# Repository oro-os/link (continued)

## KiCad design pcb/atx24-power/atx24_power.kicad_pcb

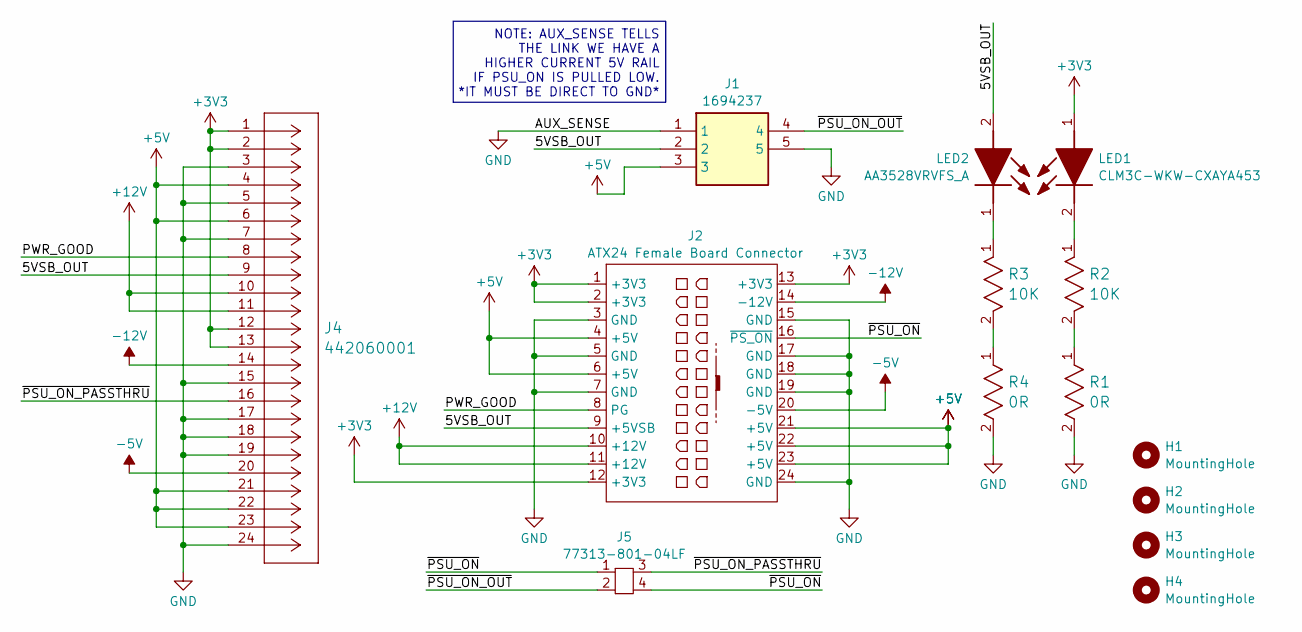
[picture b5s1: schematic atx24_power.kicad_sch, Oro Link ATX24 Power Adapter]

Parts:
H1, H2, H3, H4: MountingHole; MountingHole_3.2mm_M3
J1: 1694237; Manufacturer_Part_Number 1694237; Mouser Part Number 651-1694237
J2: ATX24 Female Board Connector; ATX24_Female_Board_Connector
J4: 442060001; CONN_SDA-44206-001_24_BP_MOL; Mouser ID 538-44206-0001
J5: 77313-801-04LF; 2x2 4p 2.54 pitch straight; Mouser ID Number 649-77313-801-04LF
LED1: CLM3C-WKW-CXAYA453; CLM3CWKWCXAYA453; Manufacturer_Part_Number CLM3C-WKW-CXAYA453; Mouser Part Number 941-CLM3CWKWCXAYA453
LED2: AA3528VRVFS_A; AA3528VRVFSA; Manufacturer_Part_Number AA3528VRVFS/A; Mouser Part Number 604-AA3528VRVFS/A
R1, R4: 0R; RES_RK73Z1E_KOA; DigiKey ID 2019-RK73Z1ETTPCT-ND
R2, R3: 10K; STA_RMCF0402_STP; DigiKey ID RMCF0402FT10K0CT-ND

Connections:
+3V3: J2.1 (+3V3), J2.2 (+3V3), J2.12 (+3V3), J2.13 (+3V3), J4.1, J4.2, J4.12, J4.13, LED1.1 (A)
+5V: J1.3, J2.4 (+5V), J2.6 (+5V), J2.21 (+5V), J2.22 (+5V), J2.23 (+5V), J4.4, J4.6, J4.21, J4.22, J4.23
+12V: J2.10 (+12V), J2.11 (+12V), J4.10, J4.11
-5V: J2.20 (-5V), J4.20
-12V: J2.14 (-12V), J4.14
/5VSB_OUT: J1.2, J2.9 (+5VSB), J4.9, LED2.2 (A)
/PWR_GOOD: J2.8 (PG), J4.8
/~PSU_ON_OUT: J1.4, J5.2
/~PSU_ON_PASSTHRU: J4.16, J5.3
/~PSU_ON: J2.16 (~PS_ON), J5.1, J5.4
GND: J1.1, J1.5, J2.3 (GND), J2.5 (GND), J2.7 (GND), J2.15 (GND), J2.17 (GND), J2.18 (GND), J2.19 (GND), J2.24 (GND), J4.3, J4.5, J4.7, J4.15, J4.17, J4.18, J4.19, J4.24, R1.2, R4.2
unnamed: LED1.2 (K), R2.1
unnamed: LED2.1 (K), R3.1
unnamed: R1.1, R2.2
unnamed: R3.2, R4.1

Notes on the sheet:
NOTE: AUX_SENSE TELLS THE LINK WE HAVE A HIGHER CURRENT 5V RAIL IF PSU_ON IS PULLED LOW. *IT MUST BE DIRECT TO GND*

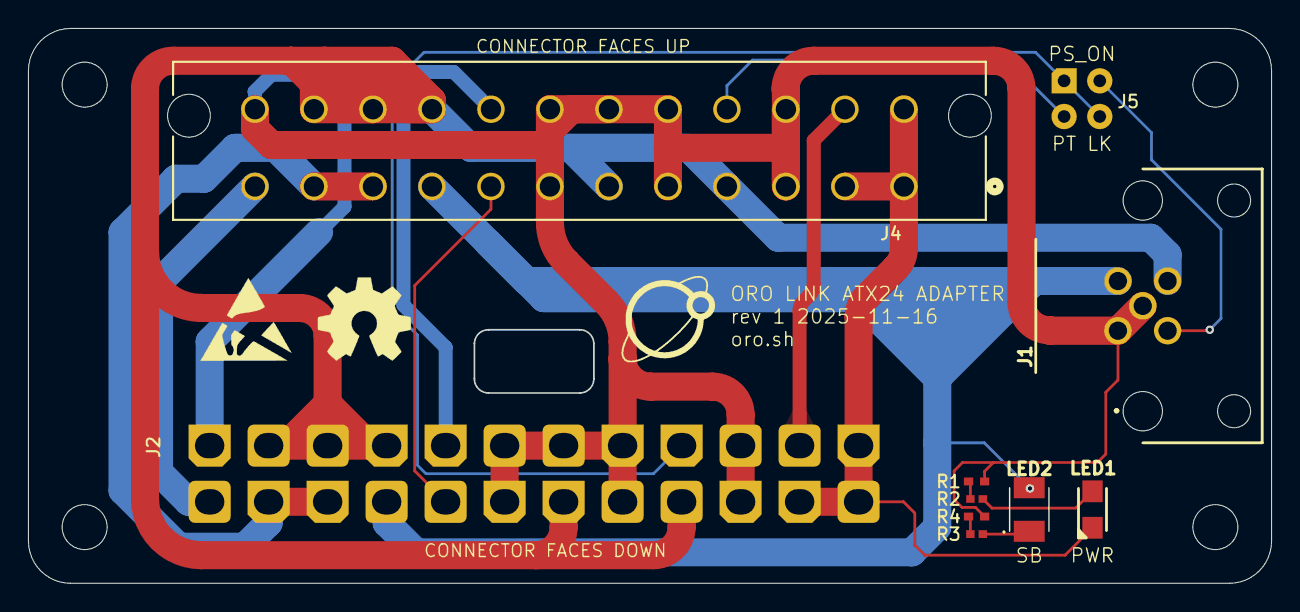
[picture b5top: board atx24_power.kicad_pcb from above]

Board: 2 copper layers, 88.5 x 39.5 mm, 14 parts (1 on the bottom side), 15 nets.

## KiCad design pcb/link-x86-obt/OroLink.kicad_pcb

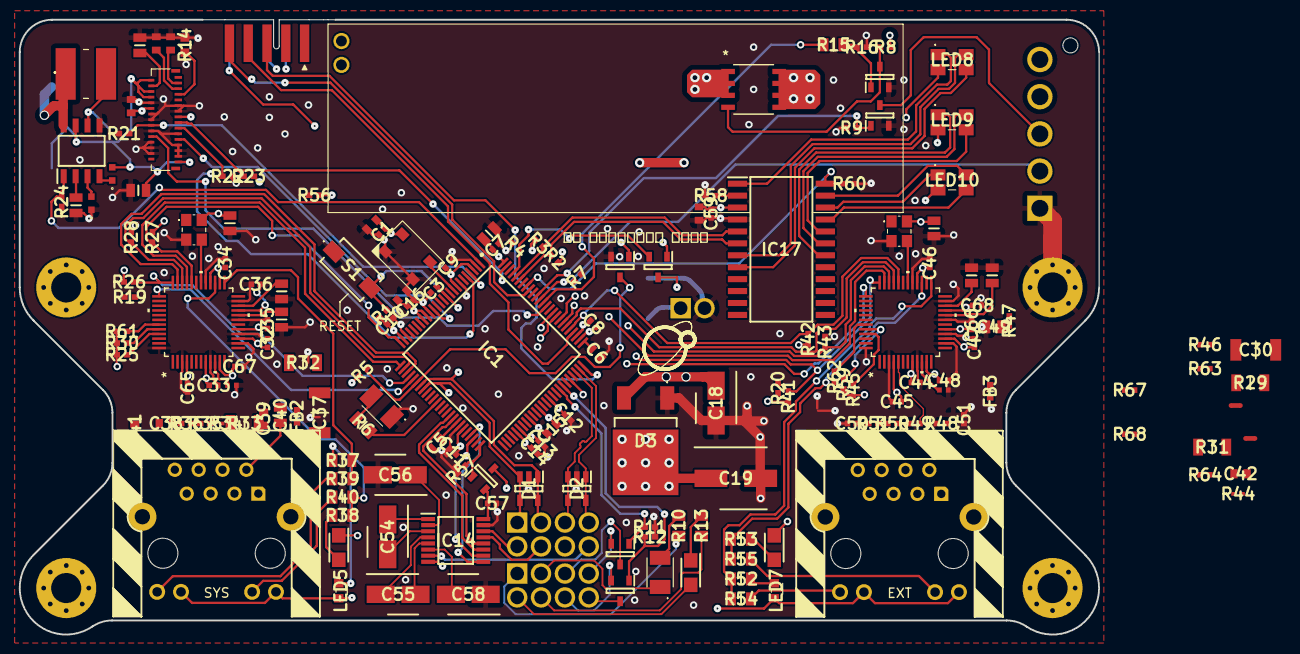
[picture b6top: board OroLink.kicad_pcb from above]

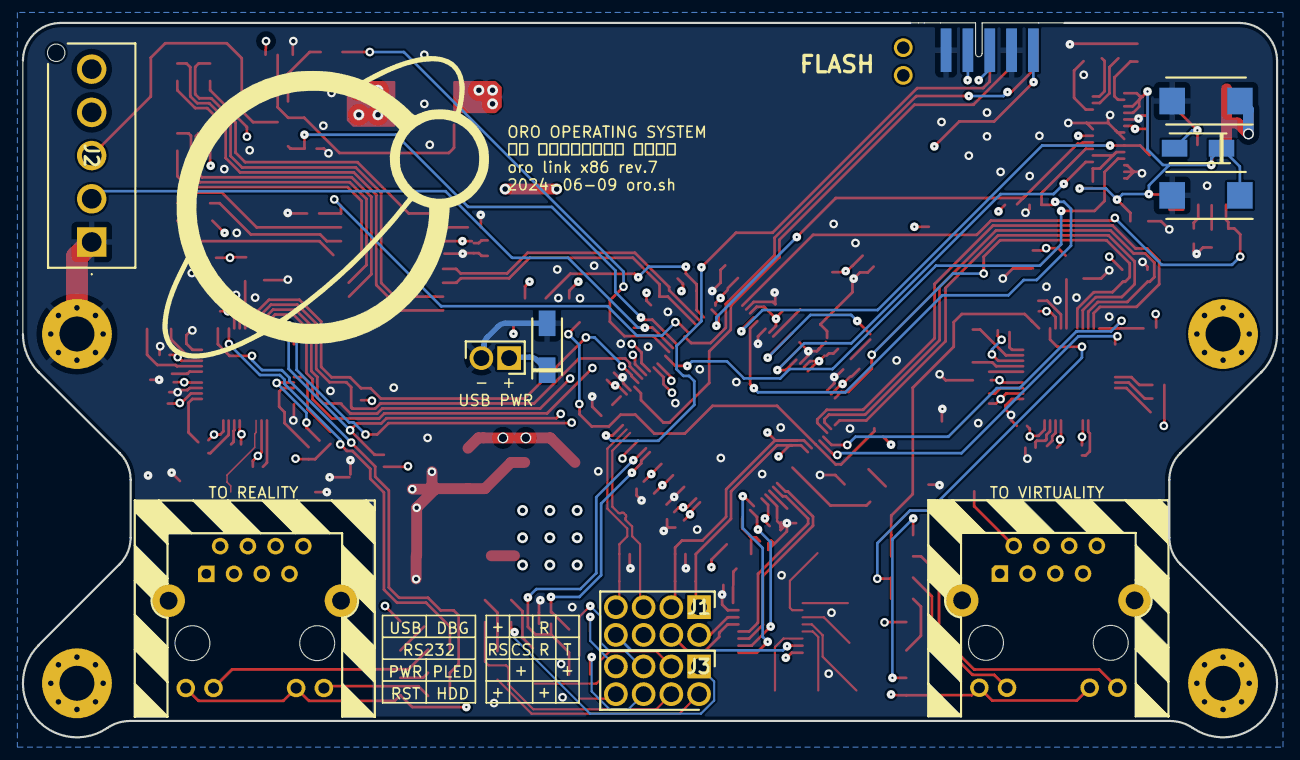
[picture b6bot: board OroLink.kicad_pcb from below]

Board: 4 copper layers, 114.9 x 65.4 mm, 183 parts (10 on the bottom side), 151 nets.

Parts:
C1, C3, C7, C8, C9, C10, C11, C12, C13, C14, C16, C32, C33, C34, C35, C36, C44, C45, C46, C47, C48, C57, C59, C65, C66, C67, C68: 0.1u; CAPC1005X33N
C2, C17, C20, C21, C23, C60: 1u; CAPC1608X90N
C4, C22, C24, C61, C62: 4.7u; CAPC2012X135N
C5, C6, C15: 2.2u; CAPC1608X90N
C18: 10u; CAPAE430X610N
C19: 22u; CAPAE660X800N
C25, C31, C40, C43, C49, C63, C64: 0.01u; CAPC2012X75N
C26: 0.047u; C1608_Commercial_Tight
C27: 0.001u; C1608_Commercial_Tight
C28, C29: 33u; CAPPM7343X310N
C30, C37: 1nF 3kV; CAPC4620X220N
C38, C39, C41, C42: 6.8nF; CAPC1608X87N
C50, C51: 22nF; CAPC1005X55N
C54, C55, C56, C58: 0.1u; CAPAE430X610N
D1, D2: ESDS302DBVR; SOT95P280X145-5N
D3: AZ1084CD-3.3TRG1; AZ1084CD33TRG1
D4, D5: SS12; DIOM5227X250N
FB1: CD54NP-180MC; CD54NP180MC
FB2, FB3: BLM18BB600SZ1D; BLM18EG121SH1D
H1, H2, H3, H4: MountingHole_Pad; MountingHole_3.2mm_M3_Pad_Via
IC1: STM32F479VGT6; QFP50P1600X1600X160-100N
IC2, IC12, IC13, IC15: PMV20ENR; SOT95P230X110-3N
IC4: TPS6734ID; SOIC127P600X175-8N
IC14: SN75C3232EPWR; SOP65P640X120-16N
IC17: IS31FL3218-GRLS2; SOIC127P1036X265-24N
J1, J3: 67996-408HLF; HDRV8W89P254_2X4_1016X483X858P
J2: DF63-5P-3.96DSA; DF635P396DSA
J4: 3-2328724-1; 323287241_flipped
J5, J6: 74990101241
J7: 2P SHORT; 2P_SHORT
J8: STLINK-V3MINIE; 009159010061911
J9: 67996-408HLF (2P CUT); HDRV8W89P254_2X4_1016X483X858P_2P
LED1, LED2: AA3528VRVFS/A; AA3528VRVFSA
LED3, LED4, LED6: CLM3C-WKW-CXAYA453; CLM3CWKWCXAYA453
LED5, LED7: APT1608VRCXF_A-5MAV; APT1608VRCXFA5MAV
LED8, LED9, LED10: 150120M173000
NT1, NT2: NetTie_2; NetTie-2_SMD_Pad0.5mm
Q1, Q2, Q3: PMV20ENR; SOT95P230X110-3N
Q4: SI4403DDY-T1-GE3; SO-8_MS-012_VIS
R1, R4, R5, R7, R8, R9, R11, R12, R16, R19, R20, R21, R22, R23, R24, R25, R26, R27, R28, R30, R41, R42, R43, R45, R56, R57, R58, R59, R60, R61, R62: 10k; RESC1005X40N
R2, R3: 4.7k; RESC1005X40N
R6, R10, R13, R15, R37, R38, R52, R53: 1k; RESC2012X60N
R14: 510K; RESC1608X55N
R17, R18: 12.4K 1%; RES_CRCW_0402
R29, R31, R32, R33: 82R <=1%; RESC3216X60N
R34, R44: 10R <=1%; RESC0603X26N
R35, R36, R50, R51: 49.9R <=1%; RESC1005X35N
R39, R40, R54, R55: 470R; RESC2012X60N
R46, R47, R48, R49, R63, R64, R67, R68: 33R <=1%; RCS0402_E3
S1: TL6400AF160QJ
U1, U2: W5500; 48LQFP_W5500_WIZ
X1: 7P-26.000MBP-T
Y1, Y2: 25MHz; ASE24576MHZLCT

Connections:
+3V3: C1.2, C2.2, C4.1, C7.2, C8.2, C9.2, C10.2, C11.2, C12.2, C13.2, C14.2, C15.1, C16.2, C17.2, C19.1, C23.2, C31.1, C32.1, C33.1, C34.1, C35.1, C36.1, C43.1, C44.1, C45.1, C46.1, C47.1, C48.1, C59.1, C60.2, C65.1, C66.1, C67.1, C68.1, D3.2 (OUTPUT), FB2.1, FB3.1, IC1.3 (VBAT), IC1.8 (VDD_1), IC1.17 (VREF+), IC1.18 (VDDA), IC1.24 (VDD_2), IC1.45 (VDD_3), IC1.55 (VDDDSI), IC1.56 (VCAPDSI), IC1.62 (VDD12DSI), IC1.65 (VDDUSB), IC1.77 (VDD_4), IC1.100 (VDD_5), IC12.3, IC15.3, IC17.3 (VCC), J4.12, J4.15, J5.9 (YLED_A), J5.11 (GLED_A), J6.9 (YLED_A), J6.11 (GLED_A), J7.1, J8.10 (VCC), LED4.1, LED5.2, LED6.1, LED7.2, LED8.2 (A_G), LED9.2 (A_G), LED10.2 (A_G), R1.1, R2.1, R3.1, R5.1, R19.2, R20.2, R23.1, R25.2, R26.2, R27.2, R30.2, R41.2, R42.2, R45.2, R59.2, R61.2, R62.2, U1.4 (AVDD), U1.8 (AVDD), U1.11 (AVDD), U1.15 (AVDD), U1.17 (AVDD), U1.21 (AVDD), U1.28 (VDD), U2.4 (AVDD), U2.8 (AVDD), U2.11 (AVDD), U2.15 (AVDD), U2.17 (AVDD), U2.21 (AVDD), U2.28 (VDD), X1.6 (VCC), Y1.4 (VDD), Y2.4 (VDD)
+5V: C18.1, C28.1, D3.3 (INPUT), FB1.1, IC4.8 (VCC), J2.5, Q4.1, Q4.2, Q4.3, R8.1
/COM Bus Header/C1+: C54.1, IC14.1 (C1+)
/COM Bus Header/C1-: C54.2, IC14.3 (C1-)
/COM Bus Header/C2+: C55.1, IC14.4 (C2+)
/COM Bus Header/C2-: C55.2, IC14.5 (C2-)
/COM Bus Header/CTS: IC1.47 (PB13), IC14.9 (ROUT2)
/COM Bus Header/EN: IC1.50 (PD8), IC15.1, R57.1
/COM Bus Header/EN_3V3: C57.1, IC14.16 (VCC), IC15.2
/COM Bus Header/RS232_CTS: IC14.8 (RIN2), J1.6
/COM Bus Header/RS232_RTS: IC14.7 (DOUT2), J1.8
/COM Bus Header/RS232_RX: IC14.13 (RIN1), J1.4
/COM Bus Header/RS232_TX: IC14.14 (DOUT1), J1.2
/COM Bus Header/RTS: IC1.48 (PB14), IC14.10 (DIN2)
/COM Bus Header/RX: IC1.42 (PB11), IC14.12 (ROUT1)
/COM Bus Header/TX: IC1.41 (PB10), IC14.11 (DIN1)
/COM Bus Header/V+: C56.1, IC14.2 (V+)
/COM Bus Header/V-: C58.2, IC14.6 (V-)
/External Ethernet/CS: IC1.80 (PA15), R42.1, U2.32 (SCSN)
/External Ethernet/ETH_RX_R+: C39.1, R31.1, R64.2
/External Ethernet/ETH_RX_R-: C42.1, R33.1, R49.2
/External Ethernet/ETH_RX_X+: C39.2, J6.1 (TD+)
/External Ethernet/ETH_RX_X-: C42.2, J6.3 (TD-)
/External Ethernet/ETH_TPIN+: R64.1, U2.6 (RXP)
/External Ethernet/ETH_TPIN-: R49.1, U2.5 (RXN)
/External Ethernet/ETH_TPOUT+: R47.1, U2.2 (TXP)
/External Ethernet/ETH_TPOUT-: R68.1, U2.1 (TXN)
/External Ethernet/ETH_TX_R+: J6.4 (RD+), R47.2, R50.1
/External Ethernet/ETH_TX_R-: J6.6 (RD-), R51.1, R68.2
/External Ethernet/GLED+: R52.2, R54.2, U2.25 (LINKLED)
/External Ethernet/RJ_EARTH: C37.1, J6.14 (MNT)
/External Ethernet/RJ_EARTH_GND: J6.8 (GNDPWR), NT2.1
/External Ethernet/SCK: IC1.81 (PC10), U2.33 (SCLK)
/External Ethernet/SDI: IC1.83 (PC12), U2.35 (MOSI)
/External Ethernet/SDO: IC1.82 (PC11), R43.2, U2.34 (MISO)
/External Ethernet/YLED+: R53.2, R55.2, U2.27 (ACTLED)
/External Ethernet/~INT: IC1.85 (PD1), R41.1, U2.36 (INTN)
/External Ethernet/~RST: IC1.84 (PD0), R20.1, U2.37 (RSTN)
/Front Panel Client/HDD+: J3.4, R13.1
/Front Panel Client/HDD-: J3.2, LED3.2
/Front Panel Client/PLED+: J3.1, R10.2
/Front Panel Client/PLED-: J3.3, LED2.1
/Front Panel Client/PWR+: J3.5, Q2.3
/Front Panel Client/PWR-: J3.7, Q2.2
/Front Panel Client/PWR_ON: IC1.68 (PC8), Q2.1, R11.1
/Front Panel Client/RESET: IC1.69 (PC9), Q3.1, R12.1
/Front Panel Client/RST+: J3.8, Q3.3
/Front Panel Client/RST-: J3.6, Q3.2
/Indicator Lights/EN: IC1.93 (PB4), IC17.24 (~SDB), R60.1
/Indicator Lights/O1: IC17.7 (O1), LED8.4 (K_R)
/Indicator Lights/O2: IC17.8 (O2), LED8.3 (K_G)
/Indicator Lights/O12: IC17.18 (O12), LED9.1 (K_B)
/Indicator Lights/O13: IC17.19 (O13), LED9.4 (K_R)
/Indicator Lights/O14: IC17.20 (O14), LED9.3 (K_G)
/Indicator Lights/O15: IC17.21 (O15), LED10.3 (K_G)
/Indicator Lights/O16: IC17.22 (O16), LED10.1 (K_B)
/Indicator Lights/O17: IC17.23 (O17), LED10.4 (K_R)
/Indicator Lights/O18: IC17.1 (O18), LED8.1 (K_B)
/Indicator Lights/SCL: IC1.95 (PB6), IC17.6 (SCL), R2.2
/Indicator Lights/SDA: IC1.96 (PB7), IC17.5 (SDA), R3.2
/Microcontroller/BOOT0: IC1.97 (BOOT0), IC12.2, R4.2
/Microcontroller/BOOT1: IC1.31 (PB2), IC13.3, R5.2
/Microcontroller/DBGUART_RX: D1.1 (NC_1), D1.5 (I/O2), IC1.32 (PE7), J1.3, J8.7 (VCP_RX)
/Microcontroller/DBGUART_TX: D1.3 (NC_2), D1.4 (I/O1), IC1.33 (PE8), J1.1, J8.8 (VCP_TX)
/Microcontroller/SWCLK: IC1.79 (PA14), J8.4 (JCLK/SWCLK)
/Microcontroller/SWDIO: IC1.75 (PA13), J8.3 (JTMS/SWDIO)
/Microcontroller/SWO: IC1.92 (PB3), J8.5 (JTDO/SWO)
/Microcontroller/SYSETH_CS: IC1.25 (PA4), R27.1, U1.32 (SCSN)
/Microcontroller/SYSETH_MISO: IC1.27 (PA6), R28.2, U1.34 (MISO)
/Microcontroller/SYSETH_SCK: IC1.26 (PA5), U1.33 (SCLK)
/Microcontroller/SYSTEH_MOSI: IC1.28 (PA7), U1.35 (MOSI)
/Microcontroller/SYSTEH_~INT: IC1.29 (PB0), R26.1, U1.36 (INTN)
/Microcontroller/SYSTEH_~RST: IC1.30 (PB1), R19.1, U1.37 (RSTN)
/Microcontroller/USB_D+: D2.1 (NC_1), D2.5 (I/O2), IC1.74 (PA12), J1.7
/Microcontroller/USB_D-: D2.3 (NC_2), D2.4 (I/O1), IC1.73 (PA11), J1.5
/Microcontroller/USB_VBUS: D5.1, IC1.71 (PA9), J9.1
/Microcontroller/VCAP1: C5.1, IC1.43 (VCAP1)
/Microcontroller/VCAP2: C6.1, IC1.76 (VCAP2)
/OLED Socket/+12V: C22.1, C27.2, C29.1, D4.1, IC4.7 (FB), J4.2, J4.6, J4.8, J4.31
/OLED Socket/CS: IC1.99 (PB9), J4.17, R23.2
/OLED Socket/DC: IC1.5 (PC14), J4.19, R22.1
/OLED Socket/ENABLE: IC1.1 (PE2), IC4.1 (EN), R24.1
/OLED Socket/SCK: IC1.87 (PD3), J4.22
/OLED Socket/SDI: IC1.15 (PC3), J4.23
/OLED Socket/~RST: IC1.4 (PC13), J4.18, R21.1
/Power Supply/5VSB_ON: J2.4, Q4.5, Q4.6, Q4.7, Q4.8
/Power Supply/PSU_ON: J2.3, Q1.3
/Power Supply/PW_OK: IC1.89 (PD5), J2.2, R7.1
/Power Supply/PW_ON: IC1.90 (PD6), Q1.1, R9.1
/Power Supply/PW_SB: IC1.88 (PD4), R15.2
/System Ethernet/ETH_RX_R+: C38.1, R29.1, R63.2
/System Ethernet/ETH_RX_R-: C41.1, R32.1, R48.2
/System Ethernet/ETH_RX_X+: C38.2, J5.1 (TD+)
/System Ethernet/ETH_RX_X-: C41.2, J5.3 (TD-)
/System Ethernet/ETH_TPIN+: R63.1, U1.6 (RXP)
/System Ethernet/ETH_TPIN-: R48.1, U1.5 (RXN)
/System Ethernet/ETH_TPOUT+: R46.1, U1.2 (TXP)
/System Ethernet/ETH_TPOUT-: R67.1, U1.1 (TXN)
/System Ethernet/ETH_TX_R+: J5.4 (RD+), R35.1, R46.2
/System Ethernet/ETH_TX_R-: J5.6 (RD-), R36.1, R67.2
/System Ethernet/GLED+: R37.2, R39.2, U1.25 (LINKLED)
/System Ethernet/RJ_EARTH: C30.1, J5.14 (MNT)
/System Ethernet/RJ_EARTH_GND: J5.8 (GNDPWR), NT1.1
/System Ethernet/YLED+: R38.2, R40.2, U1.27 (ACTLED)
GND: C1.1, C2.1, C3.2, C4.2, C5.2, C6.2, C7.1, C8.1, C9.1, C10.1, C11.1, C12.1, C13.1, C14.1, C15.2, C16.1, C17.1, C18.2, C19.2, C20.1, C21.1, C22.2, C23.1, C24.1, C25.1, C26.1, C28.2, C29.2, C30.2, C31.2, C32.2, C33.2, C34.2, C35.2, C36.2, C37.2, C40.2, C43.2, C44.2, C45.2, C46.2, C47.2, C48.2, C49.2, C50.2, C51.2, C56.2, C57.2, C58.1, C59.2, C60.1, C61.1, C62.1, C63.2, C64.2, C65.2, C66.2, C67.2, C68.2, D1.2 (GND), D2.2 (GND), D3.1 (GND), D5.2, H4.1, IC1.2 (VSS_1), IC1.7 (VSS_2), IC1.16 (VSSA), IC1.23 (VSS_3), IC1.44 (VSS_4), IC1.59 (VSSDSI), IC1.78 (VSS_5), IC2.2, IC4.5 (GND), IC13.2, IC14.15 (GND), IC17.4 (GND), J2.1, J4.10, J4.11, J4.13, J4.14, J4.16, J4.20, J4.21, J4.24, J4.25, J4.26, J4.27, J4.28, J4.29, J8.6 (GND), J8.9 (NRST), J9.2, LED1.1, NT1.2, NT2.2, Q1.2, R4.1, R7.2, R9.2, R11.2, R12.2, R14.2, R16.2, R17.2, R18.2, R21.2, R22.2, R24.2, R28.1, R43.1, R56.2, R57.2, R58.1, R60.2, S1.1 (COM), U1.3 (AGND), U1.9 (AGND), U1.14 (AGND), U1.16 (AGND), U1.19 (AGND), U1.23 (RSVD), U1.29 (GND), U1.48 (AGND), U2.3 (AGND), U2.9 (AGND), U2.14 (AGND), U2.16 (AGND), U2.19 (AGND), U2.23 (RSVD), U2.29 (GND), U2.48 (AGND), X1.1 (GND/AFC), X1.3 (GND), Y1.2 (GND/CASE), Y2.2 (GND/CASE)
unnamed: C20.2, J4.3
unnamed: C21.2, J4.5
unnamed: C24.2, J4.4
unnamed: FB2.2, R34.2, R35.2, R36.2
unnamed: FB3.2, R44.2, R50.2, R51.2
unnamed: C3.1, IC1.11 (NRST), R1.2, S1.2 (NO)
unnamed: IC1.37 (PE12), R6.1
unnamed: IC1.9 (PH0), X1.4 (CLK)
unnamed: IC2.1, R15.1, R16.1
unnamed: IC2.3, Q4.4, R8.2
unnamed: C27.1, IC4.4 (COMP)
unnamed: D4.2, FB1.2, IC4.6 (OUT)
unnamed: C25.2, IC4.2 (REF)
unnamed: C26.2, IC4.3 (SS)
unnamed: IC12.1, IC13.1, J7.2, R56.1
unnamed: IC17.2 (R_EXT), R58.2
unnamed: J4.7, R14.1
unnamed: C50.1, J5.5 (CRD), R34.1
unnamed: C40.1, J5.2 (CTD), R29.2, R32.2
unnamed: J5.12 (GLED_C), R39.1
unnamed: J5.10 (YLED_C), R40.1
unnamed: C51.1, J6.5 (CRD), R44.1
unnamed: C49.1, J6.2 (CTD), R31.2, R33.2
unnamed: J6.12 (GLED_C), R54.1
unnamed: J6.10 (YLED_C), R55.1
unnamed: LED1.2, R6.2
unnamed: LED2.2, R10.1
unnamed: LED3.1, R13.2
unnamed: LED4.2, R38.1
unnamed: LED5.1, R37.1
unnamed: LED6.2, R53.1
unnamed: LED7.1, R52.1
unnamed: C63.1, U1.22 (1V20)
unnamed: R17.1, U1.10 (EXRES1)
unnamed: R25.1, U1.45 (PMODE0)
unnamed: R30.1, U1.44 (PMODE1)
unnamed: R61.1, U1.43 (PMODE2)
unnamed: C61.2, U1.20 (TOCAP)
unnamed: U1.30 (XI/CLKIN), Y1.3 (OUTPUT)
unnamed: C64.1, U2.22 (1V20)
unnamed: R18.1, U2.10 (EXRES1)
unnamed: R45.1, U2.45 (PMODE0)
unnamed: R59.1, U2.44 (PMODE1)
unnamed: R62.1, U2.43 (PMODE2)
unnamed: C62.2, U2.20 (TOCAP)
unnamed: U2.30 (XI/CLKIN), Y2.3 (OUTPUT)

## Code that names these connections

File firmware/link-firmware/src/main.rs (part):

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	nv_ram.reboot.in_progress.write(true);

	// Begin initialization
	let debug_led1 = OutputOpenDrain::new(p.PD2, Level::High, Speed::Low);
	let debug_led2 = OutputOpenDrain::new(p.PB7, Level::High, Speed::Low);
	let debug_led3 = OutputOpenDrain::new(p.PC8, Level::High, Speed::Low);

	let ind_en = Output::new(p.PB8, Level::Low, Speed::Low);

	static I2C: StaticCell<Mutex<NoopRawMutex, i2c::I2c<'static, Blocking, i2c::mode::Master>>> =
		StaticCell::new();
	let i2c = I2C.init(Mutex::<NoopRawMutex, _>::new(i2c::I2c::new_blocking(
		p.I2C3,
		p.PA8,
		p.PC9,
		{
			let mut config = i2c::Config::default();
			config.scl_pullup = false;
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
	let _usart = usart::Uart::new_with_rtscts(
		p.USART2,
		p.PD6,
		p.PA2,
		p.PA1,
		p.PD3,
		p.DMA1_CH6,
		p.DMA1_CH5,
		Irqs,
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	)
	.unwrap();

	let usb_output_selector = Output::new(p.PA7, Level::High, Speed::Low);
	let ulpi_oc = ExtiInput::new(p.PB14, p.EXTI14, Pull::None, Irqs);
	let ulpi_rst = Output::new(p.PB15, Level::Low, Speed::Low);
	static EP_OUT_BUFFER: StaticCell<[u8; 256]> = StaticCell::new();
	let ep_out_buffer = EP_OUT_BUFFER.init([0; 256]);
	let ulpi = usb::Driver::new_hs_ulpi(
		p.USB_OTG_HS,
		Irqs,
		p.PA5,
		p.PC2,
		p.PC3,
		p.PC0,
		p.PA3,
		p.PB0,
		p.PB1,
		p.PB10,
		p.PB11,
		p.PB12,
		p.PB13,
		p.PB5,
		ep_out_buffer,
		{
			let mut config = usb::Config::default();
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		StaticCell::new();
	let spi3 = SPI3.init(Mutex::new(spi::Spi::new(
		p.SPI3,
		p.PC10,
		p.PC12,
		p.PC11,
		p.DMA1_CH7,
		p.DMA1_CH0,
		Irqs,
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		},
	)));

	let sd_oc = ExtiInput::new(p.PA6, p.EXTI6, Pull::None, Irqs);
	let sd_sense = ExtiInput::new(p.PC13, p.EXTI13, Pull::None, Irqs);
	let _sd_sense_cable = ExtiInput::new(p.PD8, p.EXTI8, Pull::None, Irqs);
	// TODO(qix-): Switch back to open drain after pullup is added
	// let sd_en = OutputOpenDrain::new(p.PC14, Level::High, Speed::Low);
	let sd_en = OutputOpenDrain::new_pull(p.PC14, Level::High, Speed::Low, Pull::Up);
	let sd_cs = OutputOpenDrain::new_pull(p.PD5, Level::High, Speed::VeryHigh, Pull::Up);
	let sd_host_sut_sel = Output::new(p.PD14, Level::Low, Speed::Low);
	let sd_spi: &'static _ = spi3;

	let syseth_int = ExtiInput::new(p.PA4, p.EXTI4, Pull::None, Irqs);
	let mut syseth_rst = Output::new(p.PC15, Level::Low, Speed::VeryHigh);
	let syseth_cs = OutputOpenDrain::new(p.PD7, Level::High, Speed::VeryHigh);
	let syseth = SpiDevice::new(spi3, syseth_cs);
	let syseth_seed = self::rand::next_u64();
	reset_wiznet_chip(&mut syseth_rst).await;
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	);

	let (_uart_tx, uart_rx) =
		usart::Uart::new(p.UART7, p.PE7, p.PE8, p.DMA1_CH1, p.DMA1_CH3, Irqs, {
			let mut config = usart::Config::default();
			config.baudrate = 3_000_000;
			config.stop_bits = usart::StopBits::STOP1;
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	let uart_rx_buffer = UART_RX_BUFFER.init([0u8; 4096]);
	let _uart_rx = uart_rx.into_ring_buffered(uart_rx_buffer);

	let exteth_int = ExtiInput::new(p.PA0, p.EXTI0, Pull::None, Irqs);
	let mut exteth_int_polarity = OutputOpenDrain::new(p.PB6, Level::Low, Speed::Low);
	exteth_int_polarity.set_low(); // Enable ethernet interrupt polarity (active low)
	let mut exteth_rst = OutputOpenDrain::new(p.PD0, Level::High, Speed::VeryHigh);
	let exteth_cs = OutputOpenDrain::new(p.PE11, Level::High, Speed::VeryHigh);
	let exteth = spi::Spi::new(
		p.SPI4,
		p.PE2,
		p.PE14,
		p.PE13,
		p.DMA2_CH1,
		p.DMA2_CH0,
		Irqs,
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		exteth_seed,
	);

	let oled_rst = Output::new(p.PD1, Level::High, Speed::Low);
	let oled_cs = OutputOpenDrain::new(p.PB9, Level::High, Speed::VeryHigh);
	let oled_dc = Output::new(p.PD4, Level::Low, Speed::VeryHigh);
	let oled_en = Output::new(p.PD9, Level::Low, Speed::Low);
	let oled = spi::Spi::new_txonly(p.SPI2, p.PA9, p.PC1, p.DMA1_CH4, Irqs, {
		let mut oledconf = spi::Config::default();
		oledconf.mode = spi::MODE_0;
		oledconf.bit_order = spi::BitOrder::MsbFirst;
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		oledconf
	});

	let _gpio2 = Output::new(p.PC7, Level::Low, Speed::Low);
	let _gpio3 = Output::new(p.PA10, Level::Low, Speed::Low);
	let _gpio4 = Output::new(p.PC6, Level::Low, Speed::Low);
	let _gpio5 = Output::new(p.PB4, Level::Low, Speed::Low);

	let vbus_oc = ExtiInput::new(p.PD15, p.EXTI15, Pull::None, Irqs);
	let vbus_en = Output::new(p.PE15, Level::Low, Speed::Low);
	let aux_vbus_sense_pin = Input::new(p.PA11, Pull::None);
	// Have we sensed the aux vbus line?
	let aux_vbus_sense = aux_vbus_sense_pin.is_low();
	crate::vars::STAT_AUX_VBUS_SENSE.set(aux_vbus_sense).await;
	let aux_vbus_oc = ExtiInput::new(p.PA12, p.EXTI12, Pull::None, Irqs);
	let aux_vbus_en = OutputOpenDrain::new(p.PA15, Level::High, Speed::Low);
	// TODO: Set `Pull::None` once external pull-up has been added
	// TODO: https://github.com/oro-os/link/issues/112
	let board_power_alert = ExtiInput::new(p.PE9, p.EXTI9, Pull::Up, Irqs);
	let psu_on = Output::new(p.PD10, Level::Low, Speed::Low);
	let _sut_pwr_switch = Output::new(p.PE12, Level::Low, Speed::Low);
	let _sut_rst_switch = Output::new(p.PE10, Level::Low, Speed::Low);

	defmt::info!("initialization complete; starting services...");
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
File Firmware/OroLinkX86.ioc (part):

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Mcu.Name=STM32F479V(G-I)Tx
Mcu.Package=LQFP100
Mcu.UserName=STM32F479VGTx
PA11.GPIOParameters=GPIO_Label
PA11.GPIO_Label=USB_D-
PA11.Mode=Device_Only
PA11.Signal=USB_OTG_FS_DM
PA12.GPIOParameters=GPIO_Label
PA12.GPIO_Label=USB_D+
PA12.Mode=Device_Only
PA12.Signal=USB_OTG_FS_DP
PA13.GPIOParameters=GPIO_Label
PA13.GPIO_Label=SWDIO
PA13.Mode=Trace_Asynchronous_SW
PA13.Signal=SYS_JTMS-SWDIO
PA14.GPIOParameters=GPIO_Label
PA14.GPIO_Label=SWCLK
PA14.Mode=Trace_Asynchronous_SW
PA14.Signal=SYS_JTCK-SWCLK
PA15.GPIOParameters=GPIO_Label
PA15.GPIO_Label=EXTETH_SS
PA15.Mode=NSS_Signal_Hard_Output
PA15.Signal=SPI3_NSS
PA2.GPIOParameters=GPIO_Label
PA2.GPIO_Label=SYSETH_EN
PA2.Signal=GPIO_Output
PA3.GPIOParameters=GPIO_Label
PA3.GPIO_Label=SYSETH_XFRM_EN
PA3.Signal=GPIO_Output
PA4.GPIOParameters=GPIO_Label
PA4.GPIO_Label=SYSETH_SS
PA4.Mode=NSS_Signal_Hard_Output
PA4.Signal=SPI1_NSS
PA5.GPIOParameters=GPIO_Label
PA5.GPIO_Label=SYSETH_SCK
PA5.Mode=Full_Duplex_Master
PA5.Signal=SPI1_SCK
PA6.GPIOParameters=GPIO_Label
PA6.GPIO_Label=SYSETH_MISO
PA6.Mode=Full_Duplex_Master
PA6.Signal=SPI1_MISO
PA7.GPIOParameters=GPIO_Label
PA7.GPIO_Label=SYSETH_MOSI
PA7.Mode=Full_Duplex_Master
PA7.Signal=SPI1_MOSI
PB0.GPIOParameters=GPIO_Label
PB0.GPIO_Label=SYSETH_INT
PB0.Signal=GPXTI0
PB1.GPIOParameters=PinState,GPIO_PuPd,GPIO_Label
PB1.GPIO_Label=SYSETH_RST
PB1.GPIO_PuPd=GPIO_NOPULL
PB1.PinState=GPIO_PIN_RESET
PB1.Signal=GPIO_Output
PB10.GPIOParameters=GPIO_Label
PB10.GPIO_Label=RS232_TX
PB10.Mode=Asynchronous
PB10.Signal=USART3_TX
PB11.GPIOParameters=GPIO_Label
PB11.GPIO_Label=RS232_RX
PB11.Mode=Asynchronous
PB11.Signal=USART3_RX
PB13.GPIOParameters=GPIO_Label
PB13.GPIO_Label=RS232_CTS
PB13.Mode=CTS_RTS
PB13.Signal=USART3_CTS
PB14.GPIOParameters=GPIO_Label
PB14.GPIO_Label=RS232_RTS
PB14.Mode=CTS_RTS
PB14.Signal=USART3_RTS
PB3.GPIOParameters=GPIO_Label
PB3.GPIO_Label=SWO
PB3.Mode=Trace_Asynchronous_SW
PB3.Signal=SYS_JTDO-SWO
PB4.GPIOParameters=GPIO_Label
PB4.GPIO_Label=INDLIGHTS_EN
PB4.Signal=GPIO_Output
PB6.GPIOParameters=GPIO_Label
PB6.GPIO_Label=INDLIGHTS_SCL
PB6.Mode=I2C
PB6.Signal=I2C1_SCL
PB7.GPIOParameters=GPIO_Label
PB7.GPIO_Label=INDLIGHTS_SDA
PB7.Mode=I2C
PB7.Signal=I2C1_SDA
PB9.GPIOParameters=GPIO_Label
PB9.GPIO_Label=OLED_SS
PB9.Mode=NSS_Signal_Hard_Output
PB9.Signal=SPI2_NSS
PC10.GPIOParameters=GPIO_Label
PC10.GPIO_Label=EXTETH_SCK
PC10.Mode=Full_Duplex_Master
PC10.Signal=SPI3_SCK
PC11.GPIOParameters=GPIO_Label
PC11.GPIO_Label=EXTETH_MISO
PC11.Mode=Full_Duplex_Master
PC11.Signal=SPI3_MISO
PC12.GPIOParameters=GPIO_Label
PC12.GPIO_Label=EXTETH_MOSI
PC12.Mode=Full_Duplex_Master
PC12.Signal=SPI3_MOSI
PC13.GPIOParameters=GPIO_Speed,GPIO_PuPd,GPIO_Label,GPIO_ModeDefaultOutputPP
PC13.GPIO_Label=OLED_RST
PC13.GPIO_ModeDefaultOutputPP=GPIO_MODE_OUTPUT_PP
PC13.GPIO_PuPd=GPIO_NOPULL
PC13.GPIO_Speed=GPIO_SPEED_FREQ_LOW
PC13.Signal=GPIO_Output
PC14/OSC32_IN.GPIOParameters=GPIO_Label
PC14/OSC32_IN.GPIO_Label=OLED_DC
PC14/OSC32_IN.Signal=GPIO_Output
PC3.GPIOParameters=GPIO_Label
PC3.GPIO_Label=OLED_MOSI
PC3.Mode=TX_Only_Simplex_Unidirect_Master
PC3.Signal=SPI2_MOSI
PC8.GPIOParameters=GPIO_Label
PC8.GPIO_Label=SYS_POWER
PC8.Signal=GPIO_Output
PC9.GPIOParameters=GPIO_Label
PC9.GPIO_Label=SYS_RESET
PC9.Signal=GPIO_Output
PD0.GPIOParameters=GPIO_PuPd,GPIO_Label
PD0.GPIO_Label=EXTETH_RST
PD0.GPIO_PuPd=GPIO_NOPULL
PD0.Signal=GPIO_Output
PD1.GPIOParameters=GPIO_Label
PD1.GPIO_Label=EXTETH_INT
PD1.Signal=GPXTI1
PD2.GPIOParameters=GPIO_Label
PD2.GPIO_Label=EXTETH_XFRM_EN
PD2.Signal=GPIO_Output
PD3.GPIOParameters=GPIO_Label
PD3.GPIO_Label=OLED_SCK
PD3.Mode=TX_Only_Simplex_Unidirect_Master
PD3.Signal=SPI2_SCK
PD4.GPIOParameters=GPIO_Label
PD4.GPIO_Label=PSU_STANDBY
PD4.Signal=GPIO_Output
PD5.GPIOParameters=GPIO_Label
PD5.GPIO_Label=PSU_OK
PD5.Signal=GPXTI5
PD6.GPIOParameters=GPIO_Label
PD6.GPIO_Label=PSU_ON
PD6.Signal=GPIO_Output
PD7.GPIOParameters=GPIO_Label
PD7.GPIO_Label=EXTETH_EN
PD7.Signal=GPIO_Output
PD8.GPIOParameters=GPIO_Label
PD8.GPIO_Label=RS232_EN
PD8.Signal=GPIO_Output
PE12.GPIOParameters=GPIO_Label
PE12.GPIO_Label=DBGLED
PE12.Signal=GPIO_Output
PE2.GPIOParameters=GPIO_Label
PE2.GPIO_Label=OLED_EN
PE2.Signal=GPIO_Output
PE7.GPIOParameters=GPIO_Label
PE7.GPIO_Label=UART_RX
PE7.Mode=Asynchronous
PE7.Signal=UART7_RX
PE8.GPIOParameters=GPIO_Label
PE8.GPIO_Label=UART_TX
PE8.Mode=Asynchronous
PE8.Signal=UART7_TX
PH0/OSC_IN.GPIOParameters=GPIO_Label
PH0/OSC_IN.GPIO_Label=CLOCK_IN
PH0/OSC_IN.Mode=HSE-External-Oscillator
PH0/OSC_IN.Signal=RCC_OSC_IN
PH1/OSC_OUT.Mode=HSE-External-Oscillator
PH1/OSC_OUT.Signal=RCC_OSC_OUT
RCC.HSE_VALUE=26000000
RCC.SYSCLKFreq_VALUE=168409090.9090909
RCC.SYSCLKSource=RCC_SYSCLKSOURCE_PLLCLK
board=custom

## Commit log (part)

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2023-07-14 add missing PSU standby enable line
2023-07-14 small tweaks
2023-07-14 tweak gerber settings
2023-07-15 add screenshot
2023-07-21 replace firmware with rust hello world firmware
2023-07-23 fix up firmware boilerplate
2023-07-23 update chip packages to latest version
2023-07-23 switch to HAL crate
2023-07-28 move to trait-based firmware initialization
2023-07-28 implement println macros for debugging
2023-07-28 add rusty-hook
2023-07-28 add ability to turn on/off serial debugging
2023-07-29 refactor to single package layout
2023-08-01 add indicator lights driver
2023-08-01 add firmware readme
2023-08-02 clean up old firmware test files
2023-08-02 add system under test controller and power on self test
2023-08-02 only run indicator lights run once during POST
2023-08-02 remove lights.rs
2023-08-03 [no-ci] initial ENC28J60 network stack code (unfinished/unpolished)
2023-08-04 initial commit for embassy-based firmware
2023-08-04 initial abstraction over devices (for embassy)
2023-08-04 move STM32F4 types to common STM32 crate
2023-08-04 configure clock on stm32f479vg variant
2023-08-04 refactor power/reset buttons to use millisecond delays
2023-08-04 increase timeout for power/reset default pulse times to 100ms
2023-08-06 successful DNS resolution
2023-08-06 increase SPI speed
2023-08-07 remove old enc28j60 code
2023-08-08 switch to defmt-brtt
2023-08-08 clean up dfmt refactor
2023-08-08 add gamma support to SSD1362 driver
2023-08-08 add minimum resistor value for current limiting resistor
2023-08-09 add oro logo display
2023-08-11 add font pipeline and basic renderer functionality
2023-08-11 always inline floor replacement
2023-08-12 add log message display
2023-08-14 add initial test monitor program
2023-08-14 initial progress font and test view
2023-08-14 re-introduce lto=fat
2023-08-14 improve percent sign in progress font
2023-08-30 add wall clock initialization
2023-08-30 resolve oro.dyn
2023-08-30 make Log view the default monitor view
2023-08-31 use more sane defaults for defmt log levels
2023-08-31 use stm32 device uid for exteth mac initialization
2023-08-31 implement rng for ethernet initialization
2023-08-31 first contact
2023-09-02 encryption and DH working
2023-09-03 remove old npmrc
2023-09-27 add timestamps to defmt logs and simplify format when running
2023-09-27 update embassy
2023-09-28 use DMA in SPI
2023-09-28 use DMA with indicator lights I2C
2023-09-28 add system ethernet and low-level ethernet frame controller
2023-09-29 implement remote pcap packet sniffing between link and SUT
2023-09-29 bind to 127.0.0.1 by default instead of 0.0.0.0
2023-10-12 break out services into their own modules
2023-10-13 add back router advertisement packet
2023-10-16 add packet tracer e-n-d::Driver implementation
2023-10-16 fix packet transmission sniffing
2023-10-16 send dhcp offer during PXE boot
2023-10-16 send dhcp ack during PXE boot
2023-10-16 clarify license wording
2023-10-17 move pxe to service
2023-10-17 use trace!() instead of debug!() in pxe service
2023-10-17 add tftp packet parsing
2023-10-17 add time service
2023-10-17 move actions daemon into firmware workspace
2023-10-17 add initial daemon service with encryption negotiation
2023-10-19 add initial protocol serialization framework
2023-10-19 remove redundant downcast
2023-10-20 move to async binser design / implementation
2023-10-20 add initial broker channel and command
2023-10-22 add initial daemon reader/writer channels (untested)
2023-10-22 fix link packet transmission
2023-10-23 move encrypted link protocol channel handling into common package
2023-10-23 obtain channels and negotiate encryption between link and daemon
2023-10-23 fix some clippy lints and remove some unused code
2023-10-23 send hello on each fresh daemon connection
2023-10-23 clear scene when switching to oro logo monitor scene
2023-10-23 pass packets directly to broker instead of translating in daemon
2023-10-24 add power transition states to protocol
2023-10-25 add 'in part' to readme license section
2023-10-26 add broker: prefix for link reset warning
2023-10-26 detect when daemon loses connection and reset
2023-10-26 swap DNS entries for oro.dyn
2023-10-26 fix logging features in daemon
2023-10-29 remove backup files from RJ45 inverter
2023-11-01 fix unbound variable error in start-oro-runner.sh
2023-11-02 initial conversion to surf and custom docker client
2023-11-02 handle github actions container spawning and lifecycle management
2023-11-06 remove old delete stopped containers request
2023-11-12 privatize Read/Write impls of protocol streams and put resources behind mutexes
2023-11-12 correctly parameterize PXE DHCP boot sizes and move to passthrough TFTP packet forwarding to daemon
2023-11-12 add serial shuttling between link and daemon
2023-11-12 use default features to help checkers find proper crates for firmware
2023-11-12 add udeps task, disabling firmware check (ref est31/cargo-udeps#153)
2023-11-17 add tftp handling to test cli
2023-11-17 set up basic test suite handling in daemon
2023-11-18 include link-test in docker image
2023-11-18 add more extensive logging to link-test
2023-11-18 make socket a+rwx
2023-11-18 press power button upon test start
2023-11-18 retry OACK packets
2023-11-18 only boot once per test session
2023-11-18 make debug led blink a bit quicker
2023-11-18 disable standby mode packets in monitor and slow down refresh rate
2023-11-18 1.0.0
2023-11-20 drop container when oro link connection dies
2023-11-20 mention that a link connection terminated even in OK case
2023-11-20 add broker test suite logic
2023-11-20 wait for docker container to exit prior to killing test session
2023-11-20 check for child exit first
2023-11-21 ignore spurious stdout/stderr errors if child has exited
2023-11-21 fix improper child status checking
2023-11-22 use x64 label instead of x86_64
2023-11-23 make link-tftp-server output serial data
2023-11-23 move x86 firmware into its own crate
2023-11-23 clean up readme, versioning, etc.
2023-11-23 fix readme assets after repository rename
2023-11-23 add readme to PCB directory
2023-11-23 add note about the PCB descriptions
2024-06-02 prepare for usb block storage impl with test repl and some tftp cleanup
2024-06-02 upgrade embassy (and fix OLED, somehow)
2024-06-02 remove dead code
2024-06-02 change clock settings to support 48k clocks
2024-06-02 update screenshot
2024-06-04 initial USB testing support
2024-06-08 add P-channel mosfet to 5VSB line
2024-06-08 increase current limiting resistor for indicator lights
2024-06-08 add VBUS and ground headers
2024-06-08 initial w5500 schematic (closes #49)
2024-06-09 rev 7 manufacture candidate
2024-06-28 initial refactor to use w5500 instead of enc28j60
2024-08-25 update oro-os organization git links
2025-03-22 next iteration of ethernet port schematic
2025-05-02 add mk8 pcb
2025-05-17 initial test of new board
2025-05-17 initial new firmware boilerplate
2025-05-17 implement power monitor
2025-05-18 add small delay when configuring power monitor chip
2025-05-18 remove debug log for power monitor and set to trace level
2025-05-21 remove trash files
2025-05-29 fix LDO pins (ref #54)
2025-05-29 ground ethernet chassis mounts (ref #58)
2025-05-29 replace 82R resistors on ethernet circuits with 49R9 (ref #60)
2025-05-29 fix ULPI PHY wiring (ref #62)
2025-05-29 fix OLED port wiring (ref #63)
2025-05-29 pull pins 1 and 3 down to ground too (ref #84)
2025-05-30 re-format OLED (ref #63), pull down DC (ref #70) and remove RST TP (closes #93)
2025-05-30 fix OLED SS capacitor value (closes #71)
2025-05-30 don't mark `ULPI_~{OC}` as a ULPI netclass
2025-05-30 add power monitor alert interrupt line (ref #82)
2025-05-30 pull up external ethernet ~{RST} line (ref #74)
2025-05-30 separate VBUS/PSU control lines (ref #89) and pull up VBUS enable (ref #68)
2025-05-30 convert an RGB backlight into 3 white channels (ref #83)
2025-05-30 replace WOL AND gate with XOR gate (ref #65)
2025-05-30 replace USB-C receptacle (ref #73)
2025-05-30 pull up `EXTETH_~{INT}_OR_WKUP (ref #66)
2025-06-02 mark usb ratings (ref #87)
2025-06-02 expose VBUS PWR only line as GPIO pin (ref #92)
2025-06-02 replace microsd slot (ref #95) and triangulate debug leds
2025-06-02 add all port mappings and low level device config
2025-06-02 some initial component placement
2025-06-02 add step file for inductor
2025-06-02 major component placement complete
2025-06-02 add pullup/down resistors to vbus enable lines
2025-06-02 pull up PS_ON and AUX_VBUS_SENSE signals (closes #68)
2025-06-02 add missing LED labels (fixes #81)
2025-06-02 touch up ratings label (fixes #87)
2025-06-02 small tweaks to ground plane
2025-06-05 put PSU ON on a MOSFET (ref #99) and fix USB THT pads
2025-06-06 reduce usart pins drastically (fixes #102)
2025-06-06 update GPIO numbering (fixes #101)
2025-06-06 fix controlled impedence values (fixes #69)
2025-06-07 initial ULPI routes
2025-06-07 switch to 8 layer board, subtract mask from edges (fixes #77)
2025-06-07 add mk9 label
2025-06-08 more routes
2025-06-08 initial complete route of mk.9
2025-06-08 add pin header silkscreen
2025-06-08 `5VPREFUSE` -> `5V PREFUSE`
2025-06-12 add more edge plating mount slots for manu (fixes #98, fixes #79)
2025-06-13 fix solder mask on bottom right detail
2025-06-13 fix 12v LDO capacitor ref-deg silkscreen
2025-11-16 update dates and finalize next mk version of link
2025-11-17 polish link and add atx24 power adapter board
2025-12-17 mk9 base firmware prep
2025-12-18 finish mk9 test firmware
2025-12-18 clean up build tools
2025-12-18 clean up dependencies a bit
2025-12-19 move new PCB files out of `pcb_new` into `pcb` and remove old `pcb`
2025-12-19 remove some outdated information from the readme
2025-12-19 move unique ID into its own module
2025-12-19 add LED controller service
2025-12-19 gest and adjust idle dimming and all LED controllers
2025-12-20 add OLED controller bus and Oro logo scene
2025-12-20 rename services and their entrypoints
2025-12-20 add flash storage support
2025-12-20 implement NVRAM and fast-reboot detection
2025-12-20 add power monitor to message bus
2026-01-13 initial configurator code
2026-02-17 add sd-adapter PCB
2026-02-18 refactor and drastically simplify services
2026-02-21 split out oled services and add init boilerplate
2026-02-21 initial working link configurator comms
2026-02-22 minor style changes
2026-02-22 initial light program debugging
2026-02-22 initial cobs stream firmware implementation
2026-02-22 working light debugging and proper frame handling
2026-02-28 add serial CLI boilerplate
2026-03-28 add pullup to sdcard EN (closes #106)
2026-03-28 add filtering caps on TPS gates (closes #107)
2026-04-03 add initial daemon resolution/connection
2026-04-03 a few schematic tweaks
2026-04-03 adjust comments
2026-04-04 remove legacy cruft in preparation for mqtt/mdns setup
2026-04-05 perform TCP connection to link
2026-04-05 init mqtt stack (and also update all deps...)
2026-04-06 include local listener for mqtt server
2026-04-08 add MQTT stats system
2026-04-08 add version and initialized stats, clean up firmware
2026-04-08 remove old 60 second timeout on socket receiver
2026-04-08 fix power state stats
2026-04-09 add initial PR fetch loop
2026-04-09 rewrite OLED power state service state machine
2026-04-09 add initial high level LED controller service
2026-04-10 initial status lights and LED selftest
2026-04-10 initial link daemon and MQTT forwarding with TLS
2026-04-11 modularize TLS negotiation connections from area controller
2026-04-11 add 4A vbus sensing and config check
2026-04-12 improve current reporting granularity and implement OC panic
2026-04-12 add vbus power driver and OC failsafes
2026-04-12 add PS_ON service and signal it for AUX VBUS switchover
2026-04-12 add USB port/header switch based on MQTT config
2026-04-12 add ulpi oc failsafe
2026-04-12 add SD OC failsafe
2026-04-16 add `orolink/register` topic announcement
2026-04-16 initial registration loop (to be thrown away)
2026-04-25 make `configured` var write-only
2026-04-25 move link-daemon/area-controller to temporary old storage
2026-05-23 cleanup before the Do It Right refactor
2026-05-31 initial update of embassy and use of `dns-srv` branch
2026-06-20 initial redis client
2026-06-20 format + add redis prefix
